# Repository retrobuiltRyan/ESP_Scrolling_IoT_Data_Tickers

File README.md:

# ESP_Scrolling_IoT_Data_Tickers
ESP8266 (or ESP32) IoT data tickers for news, weather, stocks. For those classic looking 8x8 LED matrix modules. Custom ESP8266 Node MCU 12-E PCB (just bc i have a bunch of these dev boards I need to put to use to toss) with built-in buck converter (6-28V in) and SPI headers. PCB could use one more rev to address some quirks with the ESP8266's strapping pins (rotary encoder), but project is consider 'finished'.  
https://youtu.be/6R5AQ15R8a4

API's used:
api.weather.gov
https://newsapi.org/
finnhub.io

| Reference          | Value                      | Footprint                                                                 | Qty | DNP  | DigiKey P/N             |
|--------------------|----------------------------|---------------------------------------------------------------------------|-----|------|--------------------------|
| BZ1                | Buzzer_5V                  | Buzzer_Beeper:MagneticBuzzer_ProSignal_ABT-410-RC                         | 1   | DNP     |                          |
| C1,C3,C4,C5,C6     | 0.1uF 50V                  | Capacitor_SMD:C_1206_3216Metric                                           | 5   |      | 1276-1068-1-ND           |
| C2,C7              | 0.22uF 50V CER             | Capacitor_SMD:C_1206_3216Metric                                           | 2   |      | 445-2283-1-ND            |
| D8                 | D                          | Diode_SMD:D_SMC_Handsoldering                                            | 1   | DNP  | S5AC-FDICT-ND            |
| D9                 | SMF15A                     | Diode_SMD:D_SMF                                                           | 1   |      | SMF15A-E3-08CT-ND        |
| J1                 | Barrel_Jack                | Connector_BarrelJack:BarrelJack_GCT_DCJ200-10-A_Horizontal               | 1   |      | EJ508A-ND                |
| J2,J5,J6,J10       | Screw_Terminal_2_P3.50mm   | TerminalBlock_Phoenix:PT-1,5-2-3.5-H_1x02_P3.50mm_Horizontal              | 4   |      |732-2747-ND|
| J3                 | PINHD_1x5_Male             | Connector_PinHeader_2.54mm:PinHeader_1x05_P2.54mm_Vertical               | 1   |      |  generic 0.1" breakaway header                        |
| J8                 | PINHD_1x15_Male            | Connector_PinHeader_2.54mm:PinHeader_1x15_P2.54mm_Vertical               | 1   |      |   generic 0.1" breakaway header |
| Q1                 | MOSFET P-CH 30V 25A TO252  | MOSFET_P-CH_30V_25A_TO252                                                | 1   |      | 785-1106-1-ND            |
| Q2                 | MMBT2222A                  | Package_TO_SOT_SMD:SOT-23                                                 | 1   |      | MMBT2222ATPMSCT-ND       |
| R1                 | 220                        | Resistor_SMD:R_1206_3216Metric                                            | 1   |      | 311-220FRCT-ND           |
| R2,R3,R5,R6        | 1K                         | Resistor_SMD:R_1206_3216Metric                                            | 4   |      | 311-1.00KFRCT-ND         |
| R4                 | 3.3K                       | Resistor_SMD:R_1206_3216Metric                                            | 1   |      | 311-1.00KFRCT-ND         |
| R7                 | 100k                       | Resistor_SMD:R_1206_3216Metric                                            | 1   |      | 311-100KFRCT-ND          |
| R8,R9,R10          | 10K                        | Resistor_SMD:R_1206_3216Metric                                            | 3   |      | 311-10.0KFRCT-ND         |
| SW1                | RotaryEncoder_Switch_MP    | Rotary_Encoder:RotaryEncoder_Alps_EC11E-Switch_Vertical_H20mm            | 1   | DNP     | PEC11R-4220F-S0024-ND    |
| U1                 | MAX40200AUK                | Package_TO_SOT_SMD:SOT-23-5                                               | 1   |      | 175-MAX40203AUK+TCT-ND   |
| U2                 | MP1584_Buck                | MP1584                                                                    | 1   |    [Aliexpress](https://www.aliexpress.us/item/3256806890547813.html)                         |
| U3                 | L7805                      | Package_TO_SOT_SMD:TO-252-2                                               | 1   |DNP      | 497-7255-1-ND            |

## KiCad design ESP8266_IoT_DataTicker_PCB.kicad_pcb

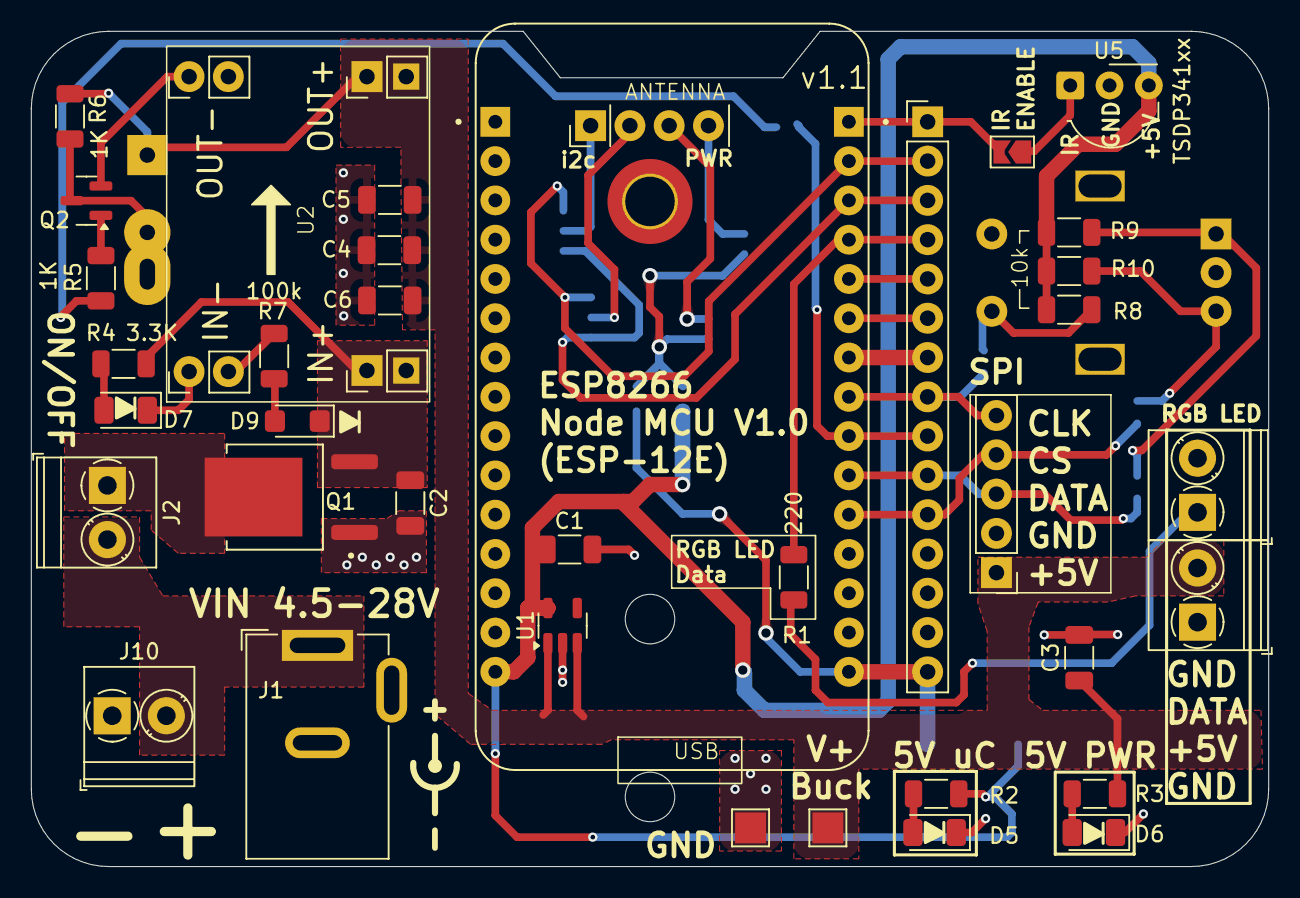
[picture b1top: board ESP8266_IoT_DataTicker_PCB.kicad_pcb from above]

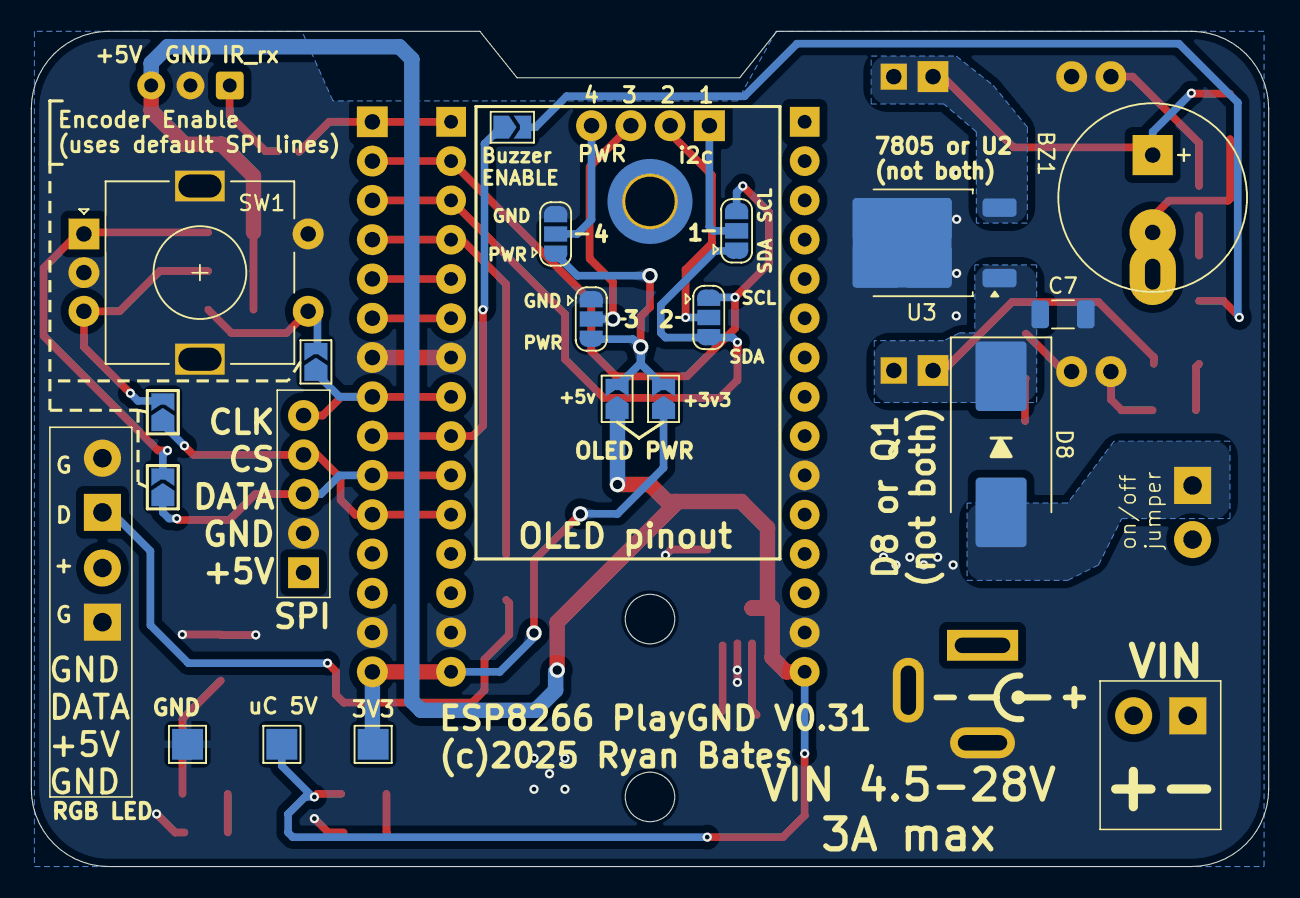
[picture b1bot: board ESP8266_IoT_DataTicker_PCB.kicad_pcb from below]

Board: 2 copper layers, 80.0 x 54.0 mm, 59 parts (18 on the bottom side), 34 nets.

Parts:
BZ1: Buzzer_5V; MagneticBuzzer_ProSignal_ABT-410-RC
C1, C3, C4, C5, C6: 0.1uF 50V; C_1206_3216Metric
C2, C7: 0.22uF 50V CER; C_1206_3216Metric
D5, D6, D7: LED; LED_1206_3216Metric
D8: D; D_SMC_Handsoldering
D9: SMF15A; D_SMF
H1: MountingHole; MountingHole_3.2mm_M3_ISO14580_Pad_TopBottom
H2, H3: MountingHole_M3; MountingHole_3.2mm_M3
J1: Barrel_Jack; BarrelJack_GCT_DCJ200-10-A_Horizontal
J2, J5, J6, J10: Screw_Terminal_2_P3.50mm; TerminalBlock_Phoenix_PT-1,5-2-3.5-H_1x02_P3.50mm_Horizontal
J3: PINHD_1x5_Male; PinHeader_1x05_P2.54mm_Vertical
J8: PINHD_1x15_Male; PinHeader_1x15_P2.54mm_Vertical
J9: PINHD_1x4_Male; PinHeader_1x04_P2.54mm_Vertical
JP1, JP3, JP5, JP6, JP9, JP10, JP11: SolderJumper_2_Open; SolderJumper-2_P1.3mm_Open_TrianglePad1.0x1.5mm
JP2, JP4, JP7, JP8: SolderJumper_3_Open; SolderJumper-3_P1.3mm_Open_RoundedPad1.0x1.5mm
Q1: MOSFET P-CH 30V 25A TO252; MOSFET_P-CH_30V_25A_TO252
Q2: MMBT2222A; SOT-23
R1: 220; R_1206_3216Metric
R2, R3, R5, R6: 1K; R_1206_3216Metric
R4: 3.3K; R_1206_3216Metric
R7: 100k; R_1206_3216Metric
R8, R9, R10: 10K; R_1206_3216Metric
SW1: RotaryEncoder_Switch_MP; RotaryEncoder_Alps_EC11E-Switch_Vertical_H20mm
TP1, TP3, TP4, TP6: uC +5V; TestPoint_Pad_2.0x2.0mm
TP2: 3V3; TestPoint_Pad_2.0x2.0mm
TP5: TestPoint; PinHeader_1x01_P1.00mm_Vertical
U1: MAX40200AUK; SOT-23-5
U2: MP1584_Buck; MP1584
U3: L7805; TO-252-2
U5: TSDP341xx; Vishay_MOLD-3Pin
v1.1: ESP8266; NodeMCU 12-E

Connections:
+5V_LED: BZ1.1, C3.1, C4.1, C5.1, C6.1, J3.1, J6.2, R3.1, R6.1, TP3.1, U1.1 (VDD), U1.3 (EN), U2.5 (OUT+), U2.6 (OUT+), U3.3 (OUT)
+BATT: J1.1, J2.2, J10.2
/1: J9.1, JP2.2 (C)
/2: J9.2, JP4.2 (C)
/3: J9.3, JP7.2 (C)
/3V3: J8.15, JP6.1 (A), TP2.1, v1.1.16 (3V3)
/4: J9.4, JP8.2 (C)
/BATT_IN: D8.2 (A), J2.1, Q1.2 (S)
/BATT_IN+: C2.1, C7.1, D8.1 (K), D9.1 (A1), Q1.3 (D), R4.1, U2.3 (IN+), U2.4 (IN+), U3.1 (IN)
/Buzzer: JP3.2 (B), R5.1
/D4(GPIO2): J8.5, v1.1.26 (D4)
/D6(GPIO12): J8.9, JP3.1 (A), v1.1.22 (D6)
/Encoder Button: JP11.2 (B), R8.1, SW1.S1
/Encoder CH_A: JP9.2 (B), R9.1, SW1.A
/Encoder CH_B: JP10.2 (B), R10.2, SW1.B
/IR_DATA: JP1.1 (A), U5.1 (OUT)
/PWR: JP5.2 (B), JP6.2 (B), JP7.3 (B), JP8.3 (B)
/RGB_DATA: J8.4, R1.2, v1.1.27 (D3)
/SCL: J8.2, JP2.1 (A), JP4.1 (A), v1.1.29 (D1)
/SDA: J8.3, JP2.3 (B), JP4.3 (B), v1.1.28 (D2)
/SPI_CLK: J3.5, J8.8, JP11.1 (A), v1.1.23 (D5)
/SPI_CS: J3.4, J8.11, JP10.1 (A), v1.1.20 (D8)
/SPI_DATA: J3.3, J8.10, JP9.1 (A), v1.1.21 (D7)
GND: C1.2, C2.2, C3.2, C4.2, C5.2, C6.2, C7.2, D5.1 (K), D6.1 (K), D7.1 (K), J1.2, J3.2, J5.2, J6.1, J8.7, J8.14, J10.1, JP7.1 (A), JP8.1 (A), Q1.1 (G), Q2.2 (E), R7.2, SW1.C, SW1.MP, SW1.S2, TP4.1, TP6.1, U1.2 (GND), U2.1 (IN-), U2.2 (IN-), U2.7 (OUT-), U2.8 (OUT-), U3.2 (GND), U5.2 (GND), v1.1.10 (GND), v1.1.14 (GND), v1.1.17 (GND), v1.1.24 (GND)
MicroContrl_+5V: C1.1, JP5.1 (A), R2.1, R8.2, R9.2, R10.1, TP1.1, U1.5 (OUT), U5.3 (Vs), v1.1.15 (VIN)
unnamed: D5.2 (A), R2.2
unnamed: D6.2 (A), R3.2
unnamed: D7.2 (A), R4.2
unnamed: D9.2 (A2), R7.1
unnamed: J5.1, R1.1
unnamed: J8.6, v1.1.25 (3V3)
unnamed: J8.1, JP1.2 (B), v1.1.30 (D0)
unnamed: Q2.1 (B), R5.2
unnamed: BZ1.2, Q2.3 (C), R6.2, TP5.1

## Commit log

2025-07-13 vector files (laser cutter)
2025-07-13 code
2025-07-13 kiCAD design files

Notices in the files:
ESP8266_IoT_DataTicker_PCB.kicad_pcb:
(c)2025 Ryan Bates
